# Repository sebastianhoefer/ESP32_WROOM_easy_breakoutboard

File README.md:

# ESP32_WROOM_easy_breakoutboard
ESP32 WROOM/ breadboard prototyping/Eagle

This is an easy-to-use ESP32 WROOM breakout board with built-in voltage regulator
and two switches for the reset and boot modes. It works well for getting started with
the ESP32 system. Feel free to optimize the board with a 3.3V UART bridge.

Have a lot of fun!

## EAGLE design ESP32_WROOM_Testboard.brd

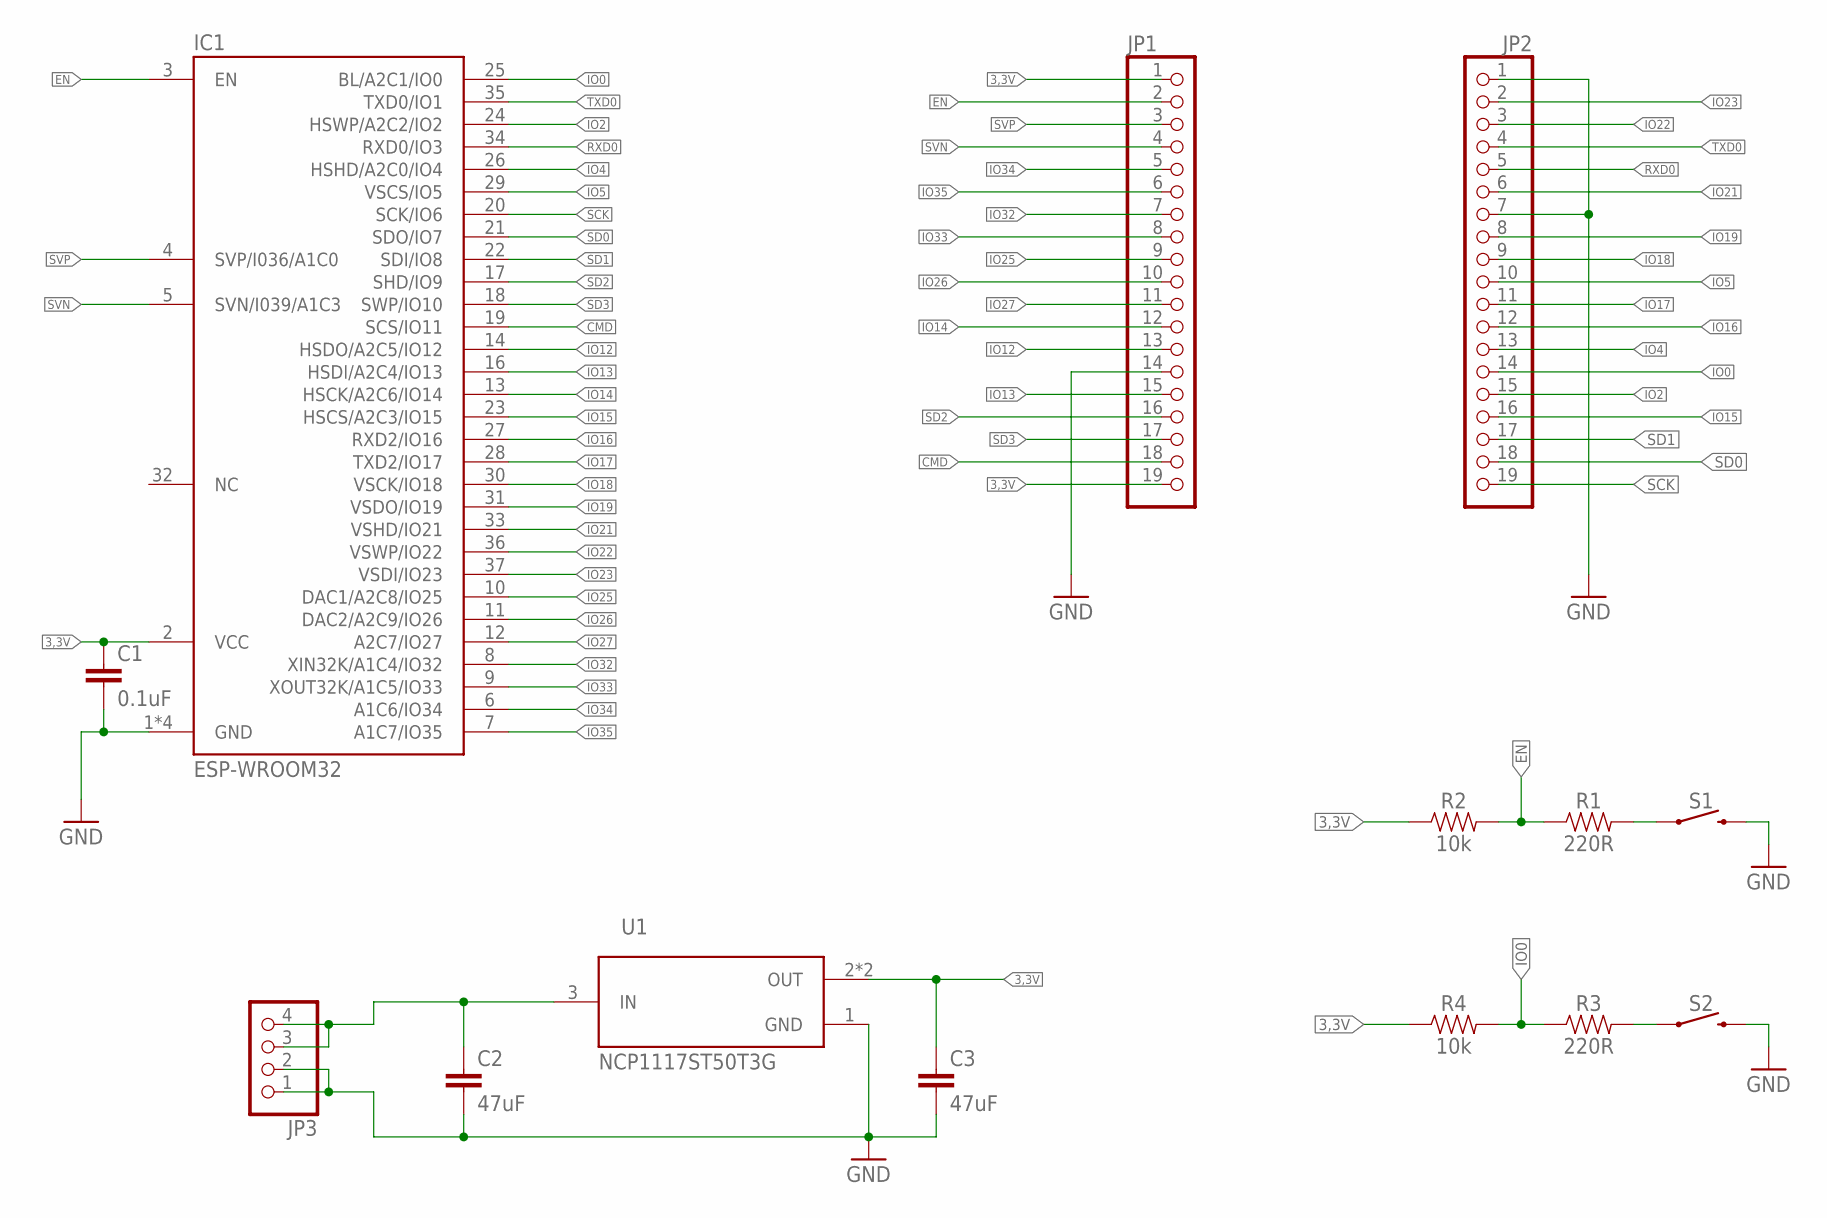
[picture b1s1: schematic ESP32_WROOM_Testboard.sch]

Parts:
C1: 0.1uF; 0603
C2, C3: 47uF; 0603
IC1: ESP-WROOM32
JP1, JP2: PINHD-1X19; 1X19
JP3: PINHD-1X4; 1X04
R1, R3: 220R; 0805
R2, R4: 10k; 0805
S1, S2: MOMENTARY-SWITCH-SPST-SMD-5.2-REDUNDANT; TACTILE_SWITCH_SMD_5.2MM
U1: NCP1117ST50T3G; SOT230P700X180-4N

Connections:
3,3V: C1.1, C3.1, IC1.2 (VCC), JP1.1, JP1.19, R2.1, R4.1, U1.2 (OUT), U1.4 (OUT)
CMD: IC1.19 (SCS/IO11), JP1.18
EN: IC1.3 (EN), JP1.2, R1.1, R2.2
GND: C1.2, C2.2, C3.2, IC1.1 (GND), IC1.15 (GND), IC1.38 (GND), IC1.TP (GND), JP1.14, JP2.1, JP2.7, JP3.1, JP3.2, S1.3 (2), S1.4 (2), S2.3 (2), S2.4 (2), U1.1 (GND)
IO0: IC1.25 (BL/A2C1/IO0), JP2.14, R3.1, R4.2
IO2: IC1.24 (HSWP/A2C2/IO2), JP2.15
IO4: IC1.26 (HSHD/A2C0/IO4), JP2.13
IO5: IC1.29 (VSCS/IO5), JP2.10
IO12: IC1.14 (HSDO/A2C5/IO12), JP1.13
IO13: IC1.16 (HSDI/A2C4/IO13), JP1.15
IO14: IC1.13 (HSCK/A2C6/IO14), JP1.12
IO15: IC1.23 (HSCS/A2C3/IO15), JP2.16
IO16: IC1.27 (RXD2/IO16), JP2.12
IO17: IC1.28 (TXD2/IO17), JP2.11
IO18: IC1.30 (VSCK/IO18), JP2.9
IO19: IC1.31 (VSDO/IO19), JP2.8
IO21: IC1.33 (VSHD/IO21), JP2.6
IO22: IC1.36 (VSWP/IO22), JP2.3
IO23: IC1.37 (VSDI/IO23), JP2.2
IO25: IC1.10 (DAC1/A2C8/IO25), JP1.9
IO26: IC1.11 (DAC2/A2C9/IO26), JP1.10
IO27: IC1.12 (A2C7/IO27), JP1.11
IO32: IC1.8 (XIN32K/A1C4/IO32), JP1.7
IO33: IC1.9 (XOUT32K/A1C5/IO33), JP1.8
IO34: IC1.6 (A1C6/IO34), JP1.5
IO35: IC1.7 (A1C7/IO35), JP1.6
unnamed: C2.1, JP3.3, JP3.4, U1.3 (IN)
unnamed: R1.2, S1.1, S1.2 (1)
unnamed: R3.2, S2.1, S2.2 (1)
RXD0: IC1.34 (RXD0/IO3), JP2.5
SCK: IC1.20 (SCK/IO6), JP2.19
SD0: IC1.21 (SDO/IO7), JP2.18
SD1: IC1.22 (SDI/IO8), JP2.17
SD2: IC1.17 (SHD/IO9), JP1.16
SD3: IC1.18 (SWP/IO10), JP1.17
SVN: IC1.5 (SVN/I039/A1C3), JP1.4
SVP: IC1.4 (SVP/I036/A1C0), JP1.3
TXD0: IC1.35 (TXD0/IO1), JP2.4

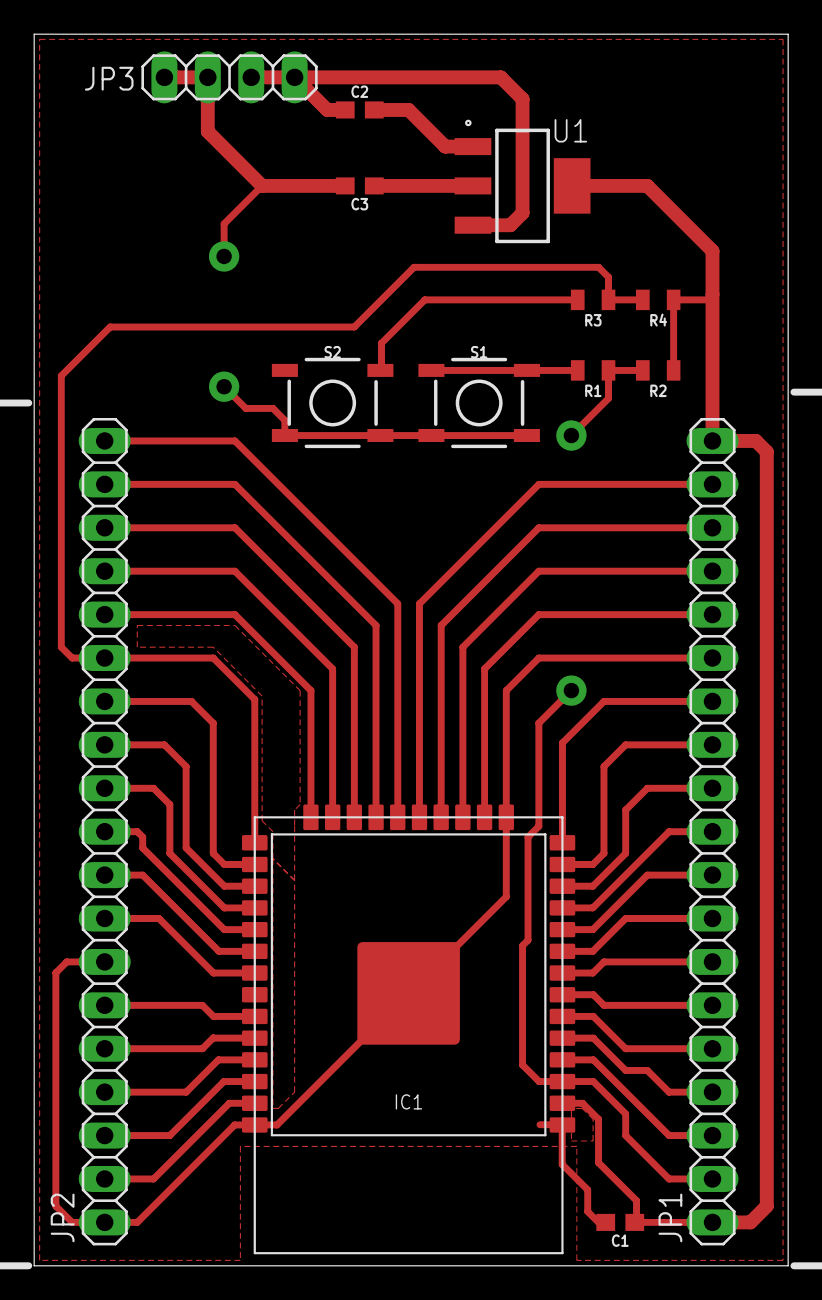
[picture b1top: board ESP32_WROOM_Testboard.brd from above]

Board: 2 copper layers, 44.1 x 72.1 mm, 14 parts (0 on the bottom side), 38 nets.

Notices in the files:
parts and their libraries:
SparkFun-Capacitors: Licensing: Creative Commons ShareAlike 4.0 International - https://creativecommons.org/licenses/by-sa/4.0
